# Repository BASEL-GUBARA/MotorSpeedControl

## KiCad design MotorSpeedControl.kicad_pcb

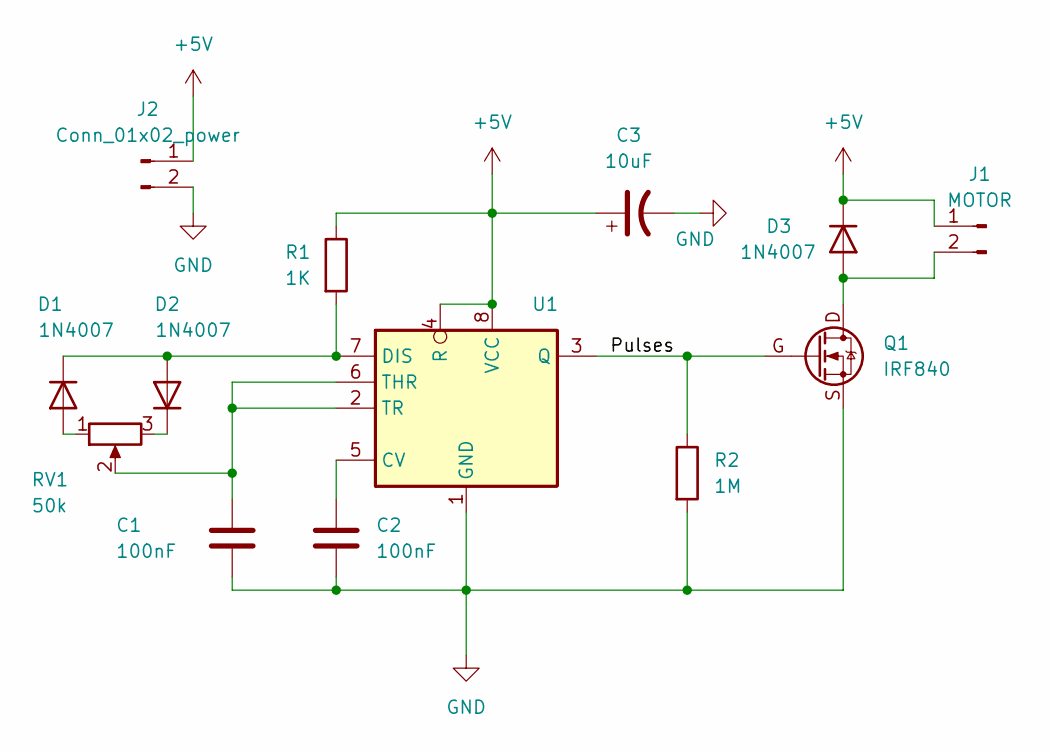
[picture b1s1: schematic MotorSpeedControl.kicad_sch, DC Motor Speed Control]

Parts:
C1, C2: 100nF; C_Axial_L5.1mm_D3.1mm_P7.50mm_Horizontal
C3: 10uF; CP_Radial_Tantal_D6.0mm_P5.00mm
D1, D2, D3: 1N4007; D_DO-41_SOD81_P7.62mm_Horizontal
J1: MOTOR; TerminalBlock_Altech_AK300-2_P5.00mm
J2: Conn_01x02_power; PinSocket_1x02_P2.54mm_Vertical
Q1: IRF840; TO-220-3_Vertical
R1: 1K; R_Axial_DIN0207_L6.3mm_D2.5mm_P7.62mm_Horizontal
R2: 1M; R_Axial_DIN0207_L6.3mm_D2.5mm_P7.62mm_Horizontal
RV1: 50k; Potentiometer_Vishay_248BH-249BH_Single_Horizontal
U1: DIP-8_W7.62mm_LongPads

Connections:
+5V: C3.1, D3.K, J1.1, J2.1, R1.1, U1.4 (R), U1.8 (VCC)
/Pulses: Q1.G, R2.1, U1.3 (Q)
GND: C1.2, C2.2, C3.2, J2.2, Q1.S, R2.2, U1.1 (GND)
unnamed: D1.A, RV1.1
unnamed: D2.K, RV1.3
unnamed: D3.A, J1.2, Q1.D
unnamed: C2.1, U1.5 (CV)
unnamed: D1.K, D2.A, R1.2, U1.7 (DIS)
unnamed: C1.1, RV1.2, U1.2 (TR), U1.6 (THR)

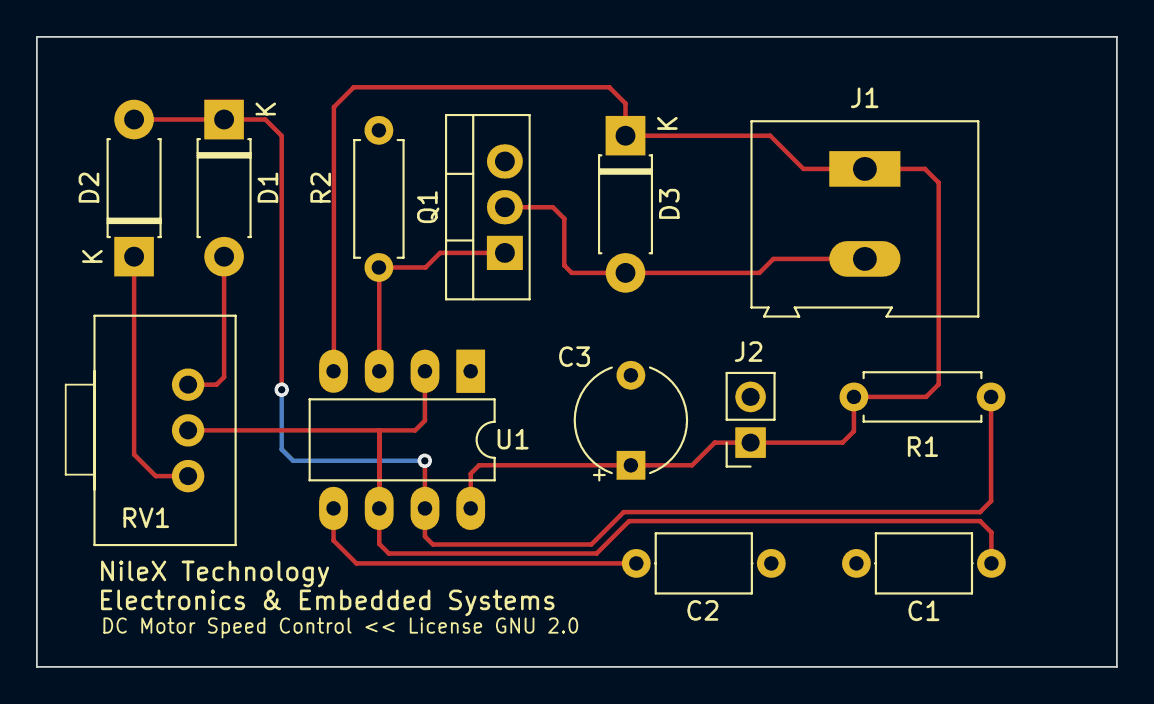
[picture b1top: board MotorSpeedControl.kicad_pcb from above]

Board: 2 copper layers, 60.0 x 35.0 mm, 13 parts (0 on the bottom side), 9 nets.

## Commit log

2023-12-29 Add files via upload
    first Upload
